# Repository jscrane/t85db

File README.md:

# t85db
Eagle schematic and board layout for a simple breadboarded ATtiny85

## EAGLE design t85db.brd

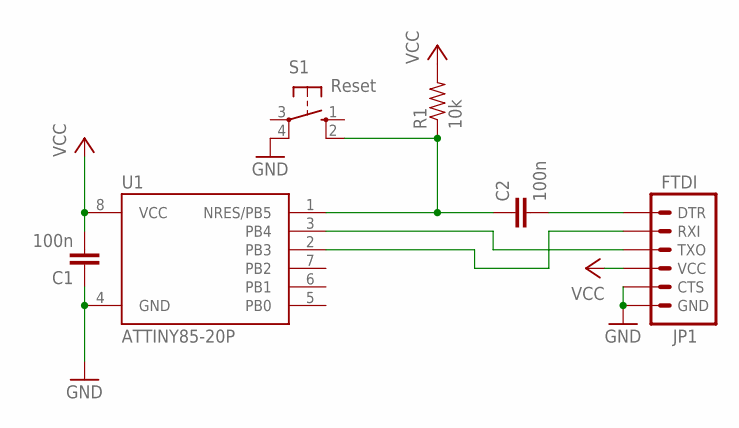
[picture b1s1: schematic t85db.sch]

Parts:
C1, C2: 100n; CAP-PTH-5MM
JP1: FTDI; 1X06
R1: 10k; AXIAL-0.1EZ
S1: Reset; B3F-10XX
U1: ATTINY85-20P; PDIP08_300MIL

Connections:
GND: C1.1, JP1.5 (CTS), JP1.6 (GND), S1.4 (P1), U1.4 (GND)
unnamed: C2.2, JP1.1 (DTR)
unnamed: JP1.3 (TXO), U1.3 (PB4)
unnamed: JP1.2 (RXI), U1.2 (PB3)
unnamed: C2.1, R1.P$1 (1), S1.2 (S1), U1.1 (NRES/PB5)
VCC: C1.2, JP1.4 (VCC), R1.P$2 (2), U1.8 (VCC)

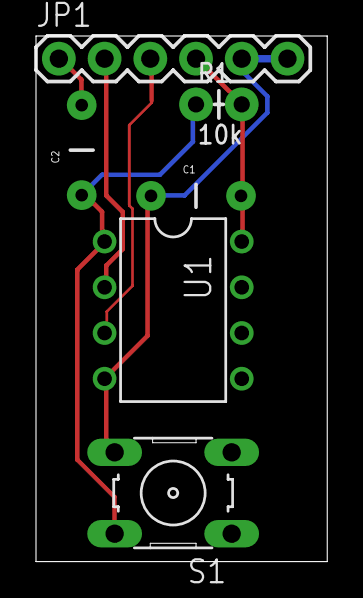
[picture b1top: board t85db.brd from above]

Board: 2 copper layers, 16.2 x 29.2 mm, 6 parts (0 on the bottom side), 6 nets.

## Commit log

2016-08-26 initial

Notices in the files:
parts and their libraries:
SparkFun-Capacitors: Licensing: CC v3.0 Share-Alike You are welcome to use this library for commercial purposes.
